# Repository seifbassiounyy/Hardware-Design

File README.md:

# Hardware-Design
PCB design for several basic schematics using Eagle.

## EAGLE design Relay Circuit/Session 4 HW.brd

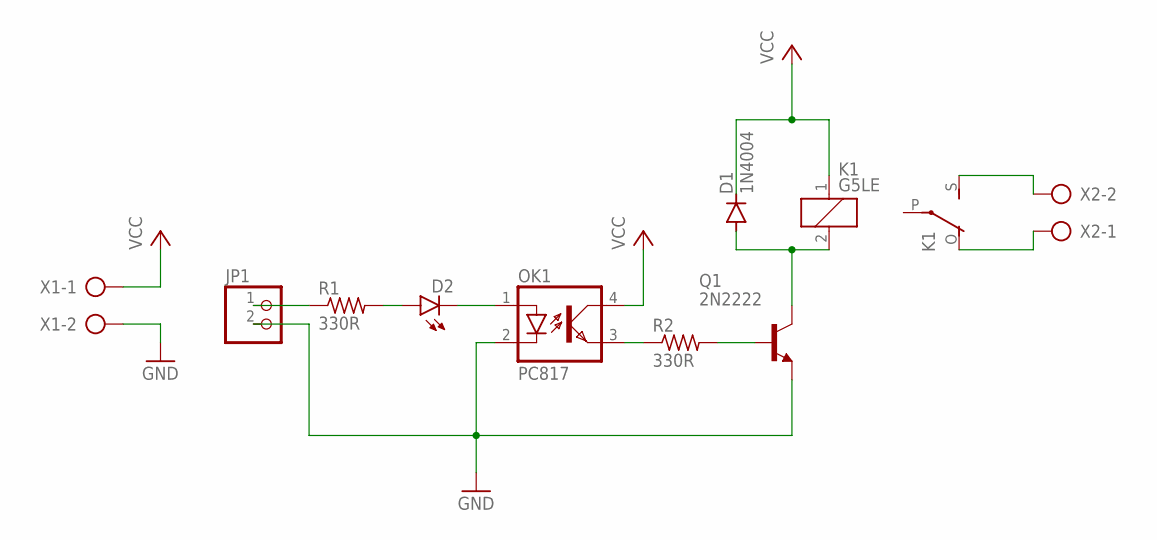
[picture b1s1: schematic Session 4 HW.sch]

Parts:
D1: 1N4004; DO41-10
D2: LED5MM
JP1: PINHD-1X2; 1X02
K1: G5LE
OK1: PC817; DIL04
Q1: 2N2222; TO18
R1, R2: 330R; 0204/7
X1, X2: AK500/2

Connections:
GND: JP1.2, OK1.2 (C), Q1.1 (E), X1.2
unnamed: Q1.2 (B), R2.2
unnamed: D2.A, R1.2
unnamed: JP1.1, R1.1
unnamed: D2.K (C), OK1.1 (A)
unnamed: OK1.3 (EMIT), R2.1
unnamed: D1.A, K1.2, Q1.3 (C)
unnamed: K1.S, X2.2
unnamed: K1.O, X2.1
VCC: D1.C, K1.1, OK1.4 (COL), X1.1

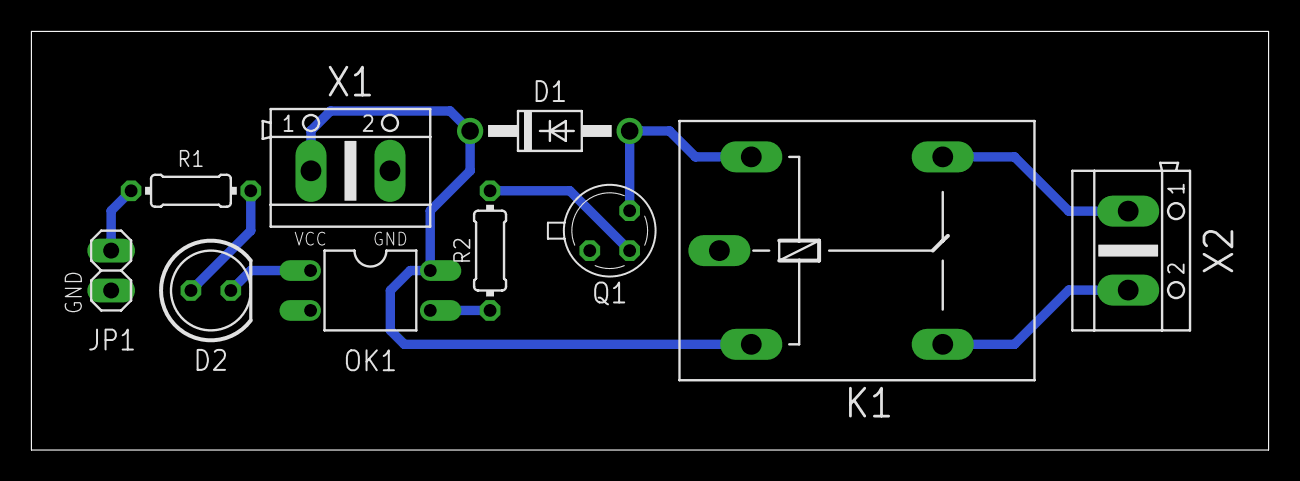
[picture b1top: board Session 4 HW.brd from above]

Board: 2 copper layers, 78.8 x 26.7 mm, 10 parts (0 on the bottom side), 10 nets.

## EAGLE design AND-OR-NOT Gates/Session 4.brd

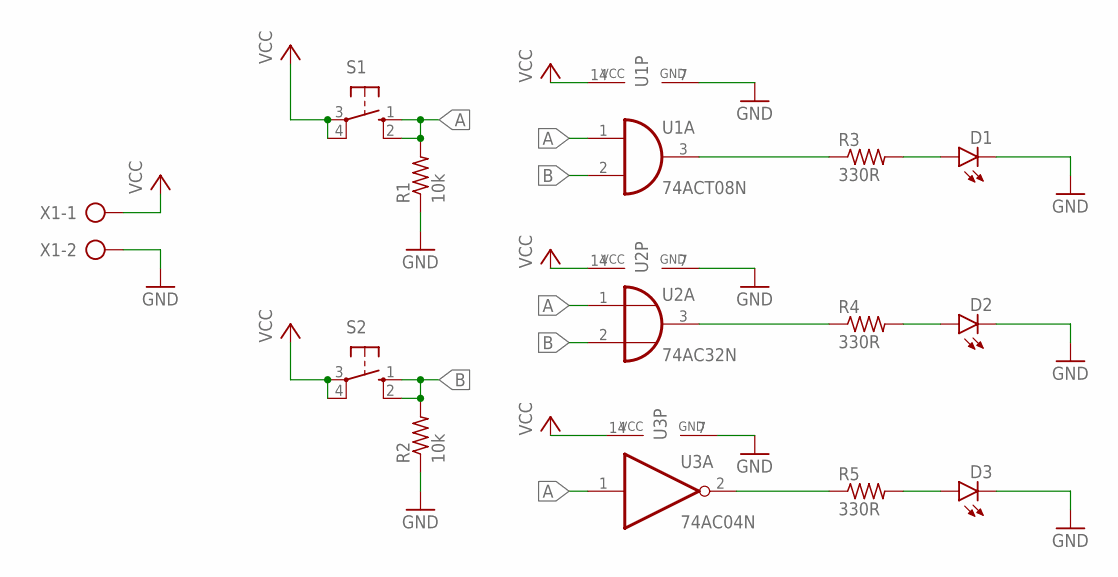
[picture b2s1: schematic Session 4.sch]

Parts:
D1, D2, D3: LED5MM
R1, R2: 10k; 0204/7
R3, R4, R5: 330R; 0204/7
S1, S2: 10-XX; B3F-10XX
U1: 74ACT08N; DIL14
U2: 74AC32N; DIL14
U3: 74AC04N; DIL14
X1: AK500/2

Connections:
A: R1.2, S1.1 (S), S1.2 (S1), U1.1 (I0), U2.1 (I0), U3.1 (I)
B: R2.2, S2.1 (S), S2.2 (S1), U1.2 (I1), U2.2 (I1)
GND: D1.K (C), D2.K (C), D3.K (C), R1.1, R2.1, U1.7 (GND), U2.7 (GND), U3.7 (GND), X1.2
unnamed: R3.1, U1.3 (O)
unnamed: D1.A, R3.2
unnamed: R5.1, U3.2 (O)
unnamed: D3.A, R5.2
unnamed: D2.A, R4.2
unnamed: R4.1, U2.3 (O)
VCC: S1.3, S1.4 (P1), S2.3, S2.4 (P1), U1.14 (VCC), U2.14 (VCC), U3.14 (VCC), X1.1

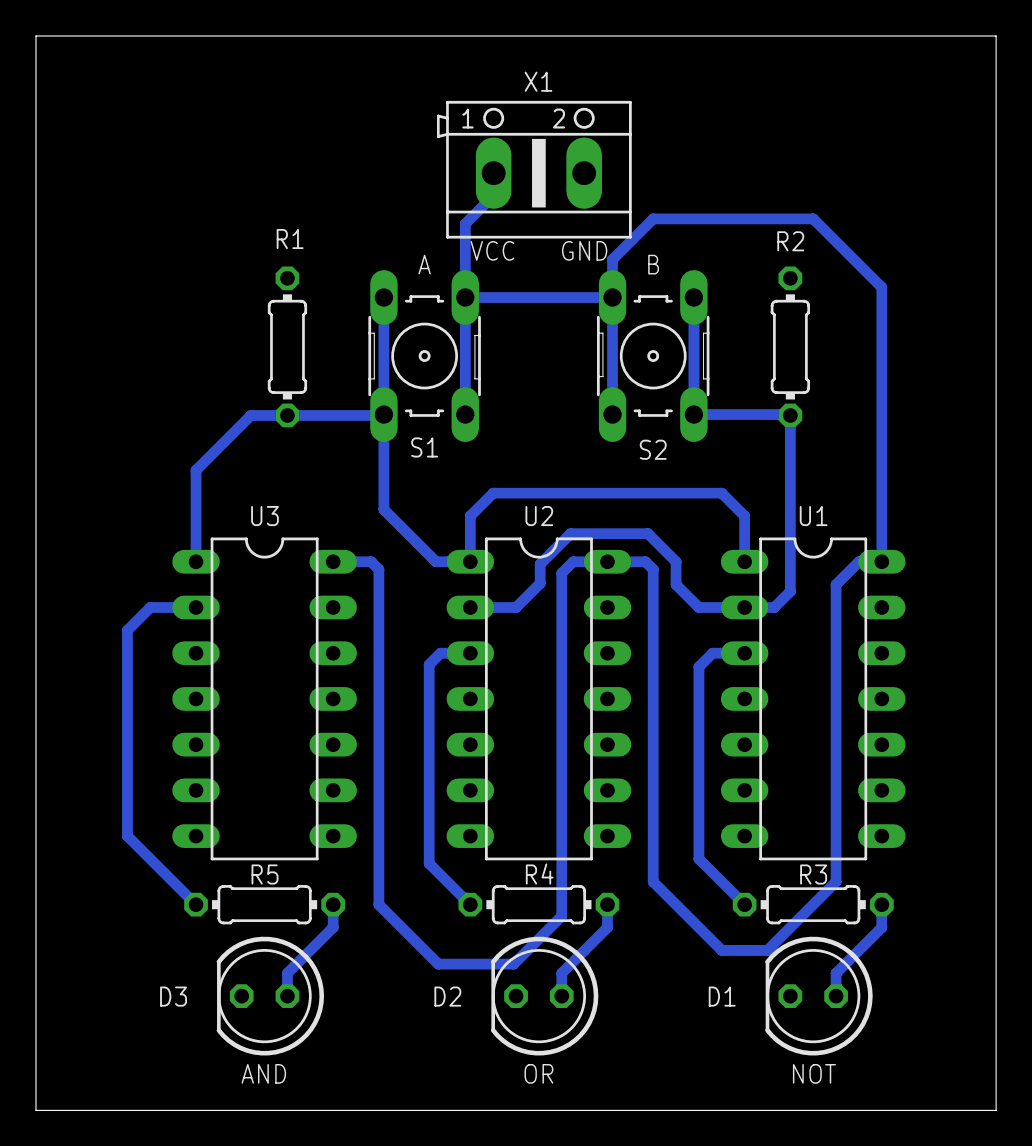
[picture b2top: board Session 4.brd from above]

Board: 2 copper layers, 53.3 x 59.7 mm, 14 parts (0 on the bottom side), 10 nets.

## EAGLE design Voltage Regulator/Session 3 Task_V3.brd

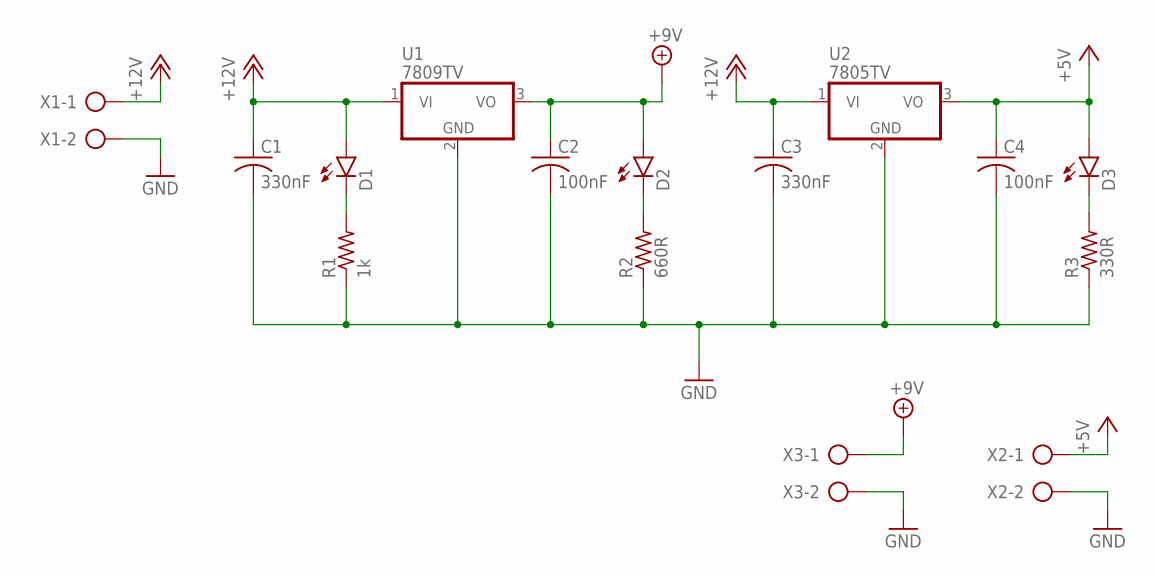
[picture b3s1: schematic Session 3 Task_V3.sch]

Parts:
C1, C3: 330nF; C025-024X044
C2, C4: 100nF; C025-024X044
D1, D2, D3: LED5MM
R1: 1k; 0204/7
R2: 660R; 0204/7
R3: 330R; 0204/7
U1: 7809TV; TO220V
U2: 7805TV; TO220V
X1, X2, X3: AK500/2

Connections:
+5V: C4.1, D3.A, U2.3 (VO), X2.1
+9V: C2.1, D2.A, U1.3 (VO), X3.1
+12V: C1.1, C3.1, D1.A, U1.1 (VI), U2.1 (VI), X1.1
GND: C1.2, C2.2, C3.2, C4.2, R1.1, R2.1, R3.1, U1.2 (GND), U2.2 (GND), X1.2, X2.2, X3.2
unnamed: D2.K (C), R2.2
unnamed: D1.K (C), R1.2
unnamed: D3.K (C), R3.2

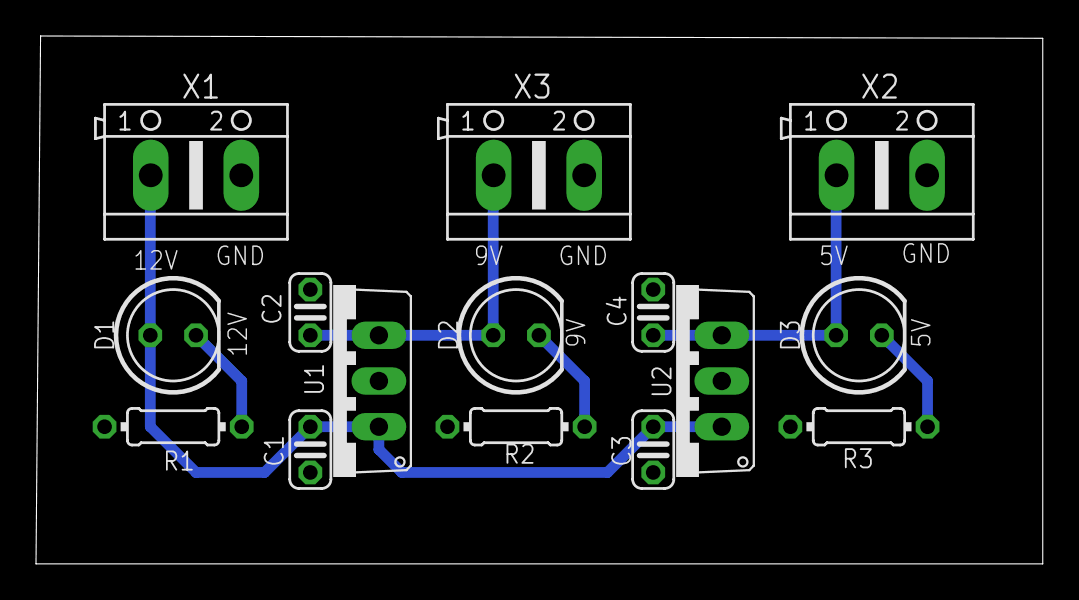
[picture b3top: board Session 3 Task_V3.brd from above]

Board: 2 copper layers, 55.9 x 29.3 mm, 15 parts (0 on the bottom side), 7 nets.

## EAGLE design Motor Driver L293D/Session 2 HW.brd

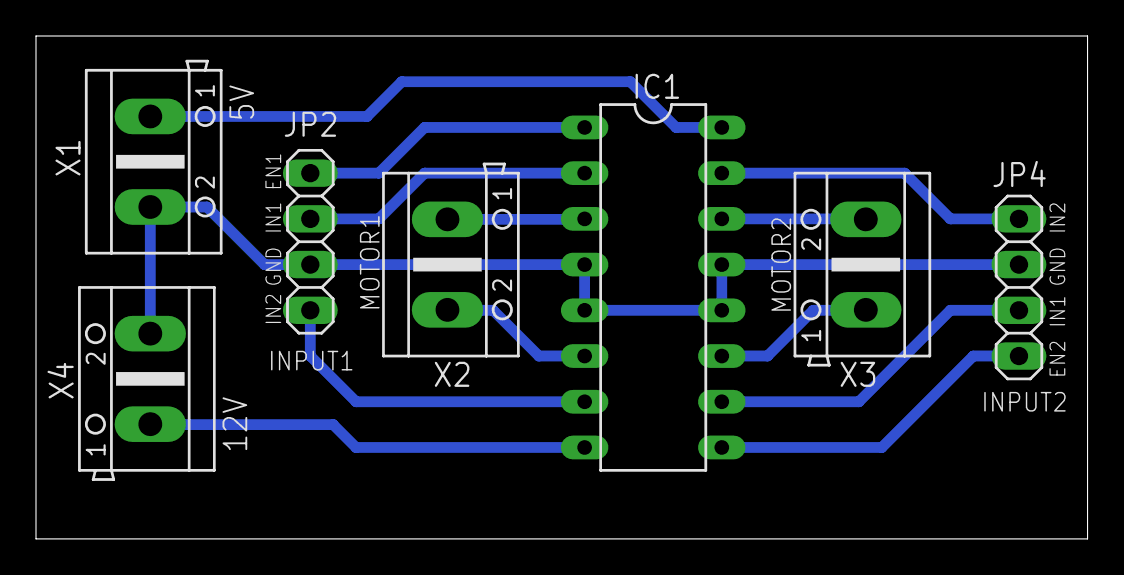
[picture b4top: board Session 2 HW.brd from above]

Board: 2 copper layers, 58.4 x 27.9 mm, 7 parts (0 on the bottom side), 13 nets.

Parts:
IC1: L293D; DIL16
JP2, JP4: 1X04
X1, X2, X3, X4: AK500/2

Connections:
+5V: IC1.16, X1.1
+12V: IC1.8, X4.1
GND: IC1.4, IC1.5, IC1.12, IC1.13, JP2.3, JP4.2, X1.2, X4.2
unnamed: IC1.1, JP2.1
unnamed: IC1.14, X3.2
unnamed: IC1.2, JP2.2
unnamed: IC1.3, X2.1
unnamed: IC1.11, X3.1
unnamed: IC1.15, JP4.1
unnamed: IC1.9, JP4.4
unnamed: IC1.6, X2.2
unnamed: IC1.10, JP4.3
unnamed: IC1.7, JP2.4

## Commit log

2023-08-18 Add files via upload
    Voltage regulation circuit from +12V to +9V and +5V using 7809 and 7805 regulators
